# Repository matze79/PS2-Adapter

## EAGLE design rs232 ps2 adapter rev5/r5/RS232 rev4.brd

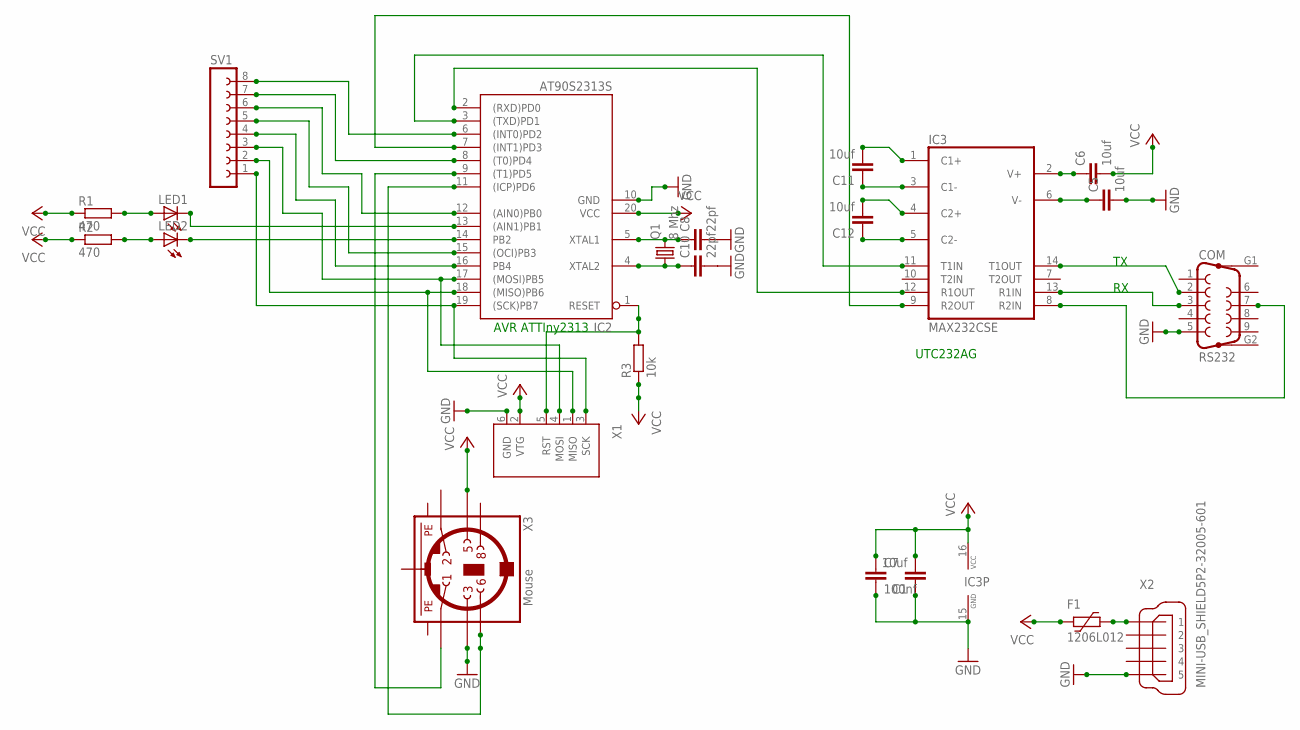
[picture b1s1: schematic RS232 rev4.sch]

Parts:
C1, C5, C6, C11, C12: 10uf; C1206K
C7: 100nf; C1206
C8, C10: 22pf; C1206
COM: RS232; F09HP
F1: 1206L012; 1206L
IC2: AT90S2313S; SO20L
IC3: MAX232CSE; SO16
LED1, LED2: LEDCHIPLED_0805; CHIPLED_0805
Q1: 8 Mhz; HC49/S
R1, R2: 470; R1206
R3: 10k; R1206
SV1: FE08-1; FE08
X1: AVRISP6PINHEADER; 6PINHEADER
X2: MINI-USB_SHIELD5P2-32005-601; 32005-601
X3: Mouse; M_DIN6

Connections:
GND: C1.1, C5.2, C7.2, C8.2, C10.2, COM.5, IC2.10 (GND), IC3.15 (GND), X1.6 (GND), X2.5, X3.3
unnamed: IC2.3 ((TXD)PD1), IC3.11 (T1IN)
unnamed: IC2.2 ((RXD)PD0), IC3.12 (R1OUT)
unnamed: C11.1, IC3.3 (C1-)
unnamed: C11.2, IC3.1 (C1+)
unnamed: C12.2, IC3.4 (C2+)
unnamed: C12.1, IC3.5 (C2-)
unnamed: IC2.1 (RESET), R3.2, X1.5 (RST)
unnamed: IC2.11 ((ICP)PD6), X3.6
unnamed: COM.2, IC3.14 (T1OUT)
unnamed: IC2.7 ((INT1)PD3), IC3.9 (R2OUT)
unnamed: C8.1, IC2.5 (XTAL1), Q1.2
unnamed: IC2.14 (PB2), LED2.C
unnamed: C5.1, IC3.6 (V-)
unnamed: C6.1, IC3.2 (V+)
unnamed: IC2.13 ((AIN1)PB1), LED1.C
unnamed: COM.3, IC3.13 (R1IN)
unnamed: C10.1, IC2.4 (XTAL2), Q1.1
unnamed: LED2.A, R2.2
unnamed: LED1.A, R1.2
unnamed: IC2.9 ((T1)PD5), X3.1
unnamed: F1.1, X2.1
PB2: IC2.12 ((AIN0)PB0), SV1.6
PB3: IC2.15 ((OCI)PB3), SV1.5
PB4: IC2.16 (PB4), SV1.4
PB5: IC2.17 ((MOSI)PB5), SV1.3, X1.4 (MOSI)
PB6: IC2.18 ((MISO)PB6), SV1.2, X1.1 (MISO)
PB7: IC2.19 ((SCK)PB7), SV1.1, X1.3 (SCK)
PD2: IC2.6 ((INT0)PD2), SV1.8
PD4: IC2.8 ((T0)PD4), SV1.7
PE1: X3.SH1 (PE1)
PE2: X3.SH2 (PE2)
PE3: X3.SH3 (PE3)
SERIAL#: COM.7, IC3.8 (R2IN)
VCC: C1.2, C6.2, C7.1, F1.2, IC2.20 (VCC), IC3.16 (VCC), R1.1, R2.1, R3.1, X1.2 (VTG), X3.5

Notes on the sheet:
AVR ATTIny2313
UTC232AG

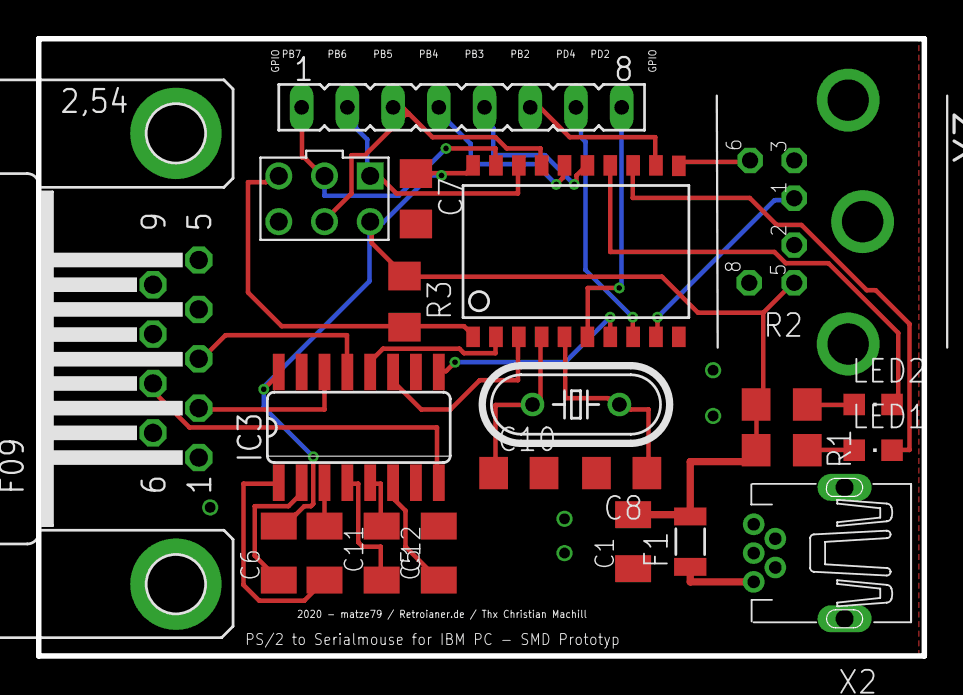
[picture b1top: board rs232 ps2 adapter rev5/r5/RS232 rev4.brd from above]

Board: 2 copper layers, 49.2 x 34.3 mm, 22 parts (0 on the bottom side), 32 nets.

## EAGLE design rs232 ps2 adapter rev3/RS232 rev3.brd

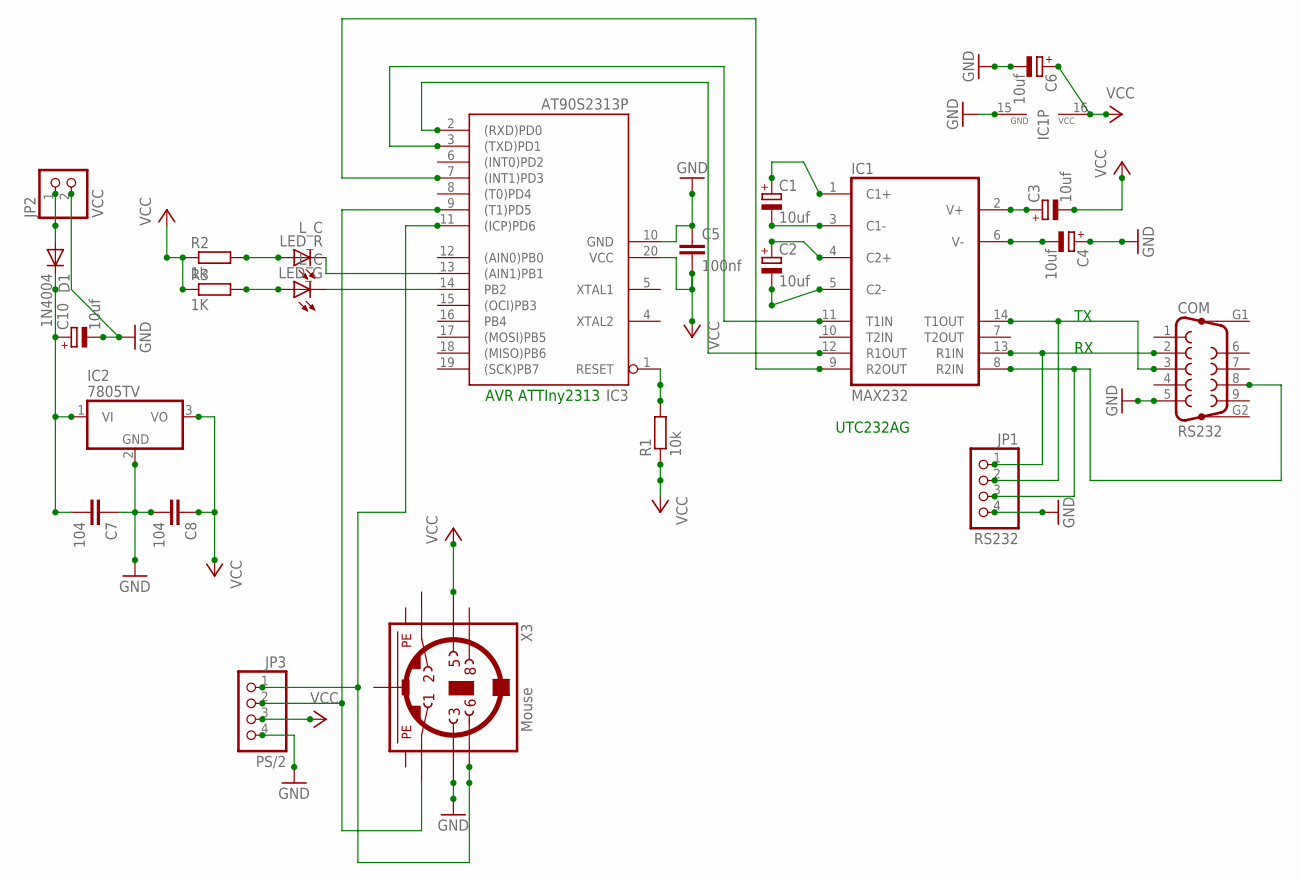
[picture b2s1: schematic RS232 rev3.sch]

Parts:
C1, C2, C3, C4, C6, C10: 10uf; E2,5-6E
C5: 100nf; C2.5-3
C7, C8: 104; C025-025X050
COM: RS232; F09HP
D1: 1N4004; DO41-10
IC1: MAX232; DIL16
IC2: 7805TV; TO220V
IC3: AT90S2313P; DIL20
JP1: RS232; 1X04
JP2: VCC; 1X02
JP3: PS/2; 1X04
LED_G: L_C; LED3MM
LED_R: L_C; LED3MM
R1: 10k; 0207/7
R2: 1k; 0309V
R3: 1K; 0309V
X3: Mouse; M_DIN6

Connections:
GND: C4.+, C5.1, C6.-, C7.1, C8.2, C10.-, COM.5, IC1.15 (GND), IC2.2 (GND), IC3.10 (GND), JP1.4, JP2.2, JP3.4, X3.3
unnamed: IC1.11 (T1IN), IC3.3 ((TXD)PD1)
unnamed: IC1.12 (R1OUT), IC3.2 ((RXD)PD0)
unnamed: C1.-, IC1.3 (C1-)
unnamed: C1.+, IC1.1 (C1+)
unnamed: C2.+, IC1.4 (C2+)
unnamed: C2.-, IC1.5 (C2-)
unnamed: IC3.1 (RESET), R1.2
unnamed: IC3.11 ((ICP)PD6), JP3.1, X3.6
unnamed: C7.2, C10.+, D1.C, IC2.1 (VI)
unnamed: IC1.9 (R2OUT), IC3.7 ((INT1)PD3)
unnamed: IC3.14 (PB2), LED_G.K (C)
unnamed: C4.-, IC1.6 (V-)
unnamed: C3.+, IC1.2 (V+)
unnamed: IC3.13 ((AIN1)PB1), LED_R.K (C)
unnamed: COM.2, IC1.13 (R1IN), JP1.1
unnamed: COM.3, IC1.14 (T1OUT), JP1.2
unnamed: LED_G.A, R3.2
unnamed: LED_R.A, R2.2
unnamed: IC3.9 ((T1)PD5), JP3.2, X3.1
PE1: X3.SH1 (PE1)
PE2: X3.SH2 (PE2)
PE3: X3.SH3 (PE3)
POWER: D1.A, JP2.1
SERIAL#: COM.8, IC1.8 (R2IN), JP1.3
VCC: C3.-, C5.2, C6.+, C8.1, IC1.16 (VCC), IC2.3 (VO), IC3.20 (VCC), JP3.3, R1.1, R2.1, R3.1, X3.5

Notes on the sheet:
AVR ATTIny2313
UTC232AG

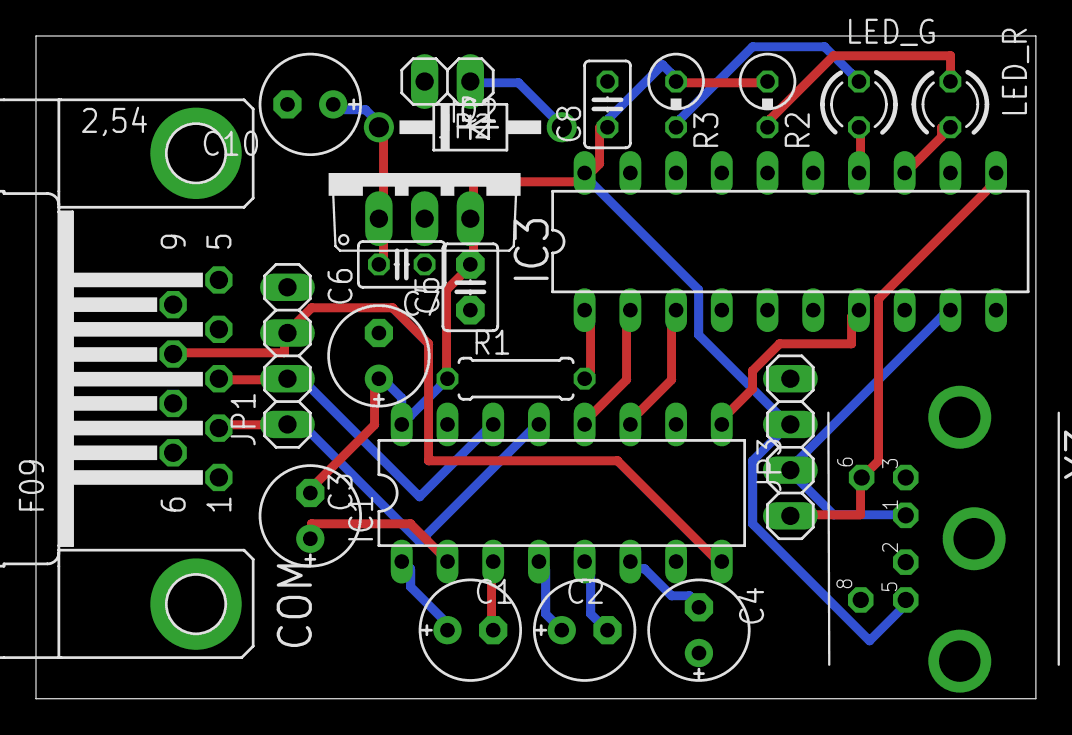
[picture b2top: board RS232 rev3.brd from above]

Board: 2 copper layers, 55.6 x 36.8 mm, 23 parts (0 on the bottom side), 23 nets.

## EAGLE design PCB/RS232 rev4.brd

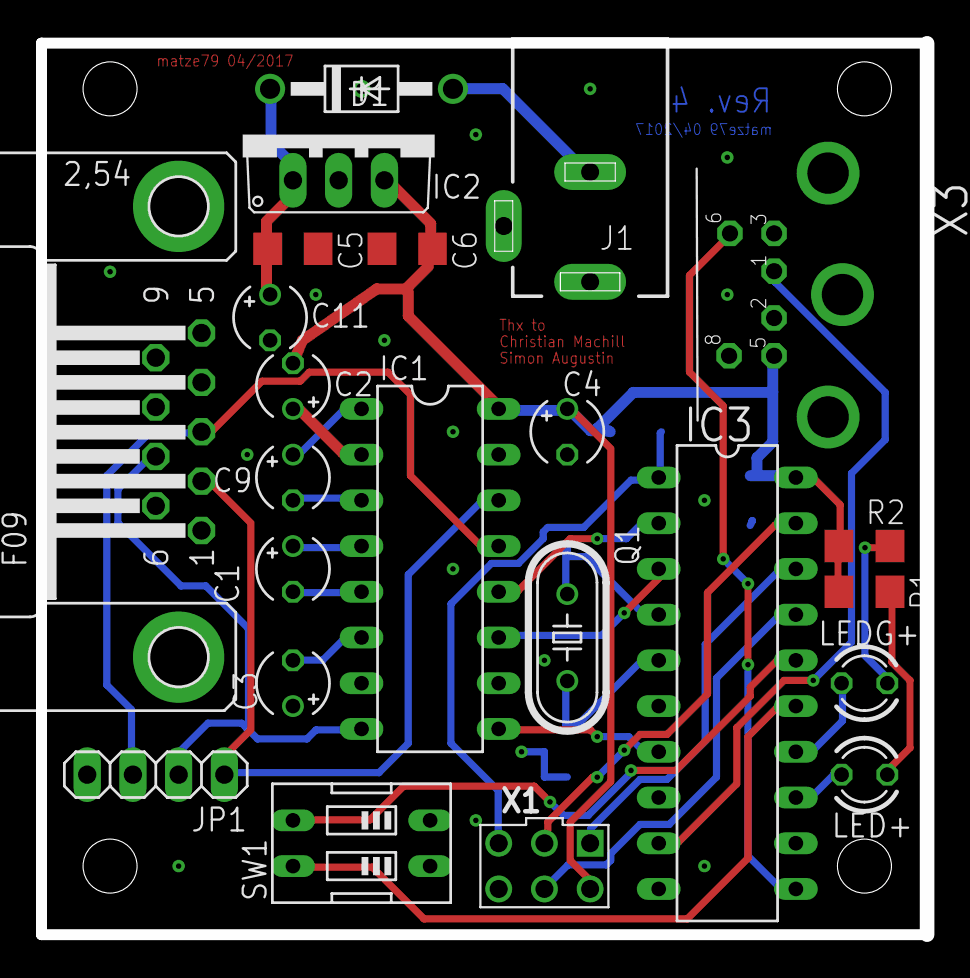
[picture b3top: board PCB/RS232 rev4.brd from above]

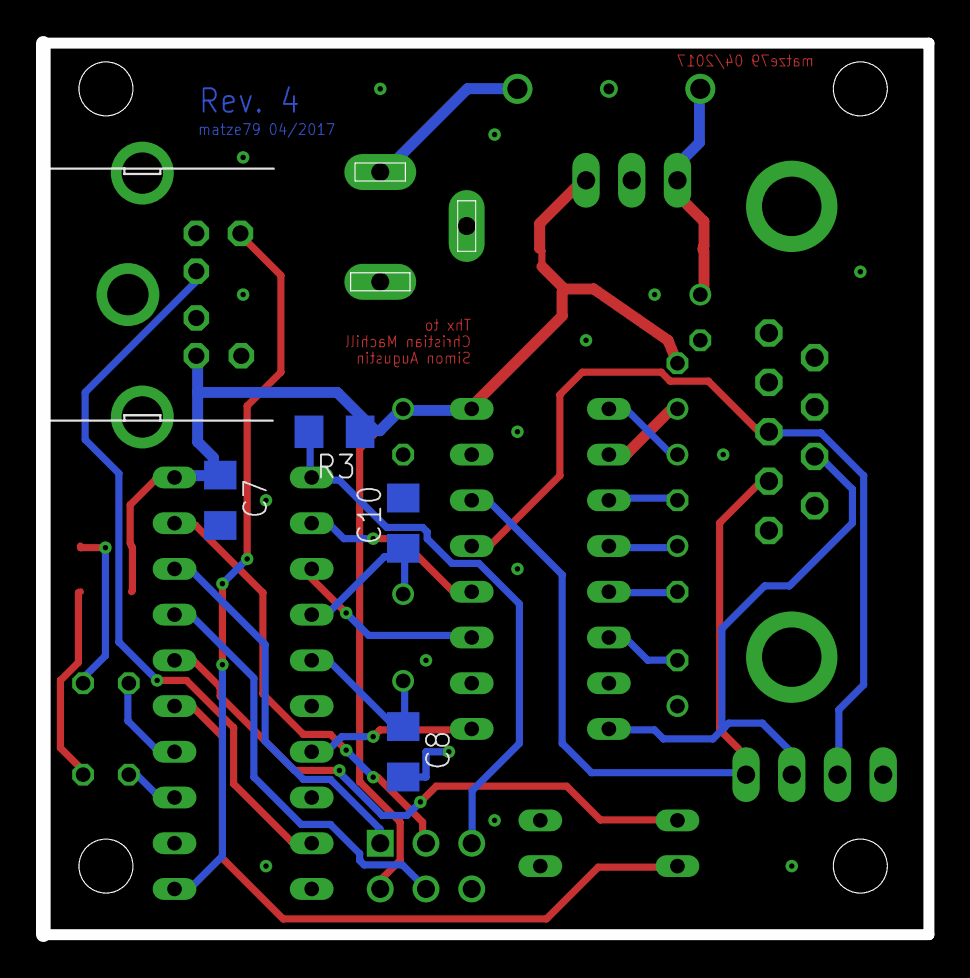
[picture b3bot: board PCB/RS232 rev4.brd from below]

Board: 2 copper layers, 49.1 x 49.5 mm, 27 parts (4 on the bottom side), 30 nets.

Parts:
C1, C2, C3, C4, C9: 10uf; TT2D4
C5, C6, C7: 100nf; C1206
C8, C10: 22pf; C1206
C11: 100uf; TT2D4
COM: RS232; F09HP
D1: 1N4004; DO41-10
IC1: MAX232; DIL16
IC2: 7805TV; TO220V
IC3: AT90S2313P; DIL20
J1: DCJ0202
JP1: RS232; 1X04
LED+: L_C; LED3MM
LEDG+: L_C; LED3MM
Q1: 8 Mhz; HC49/S
R1, R2: 470; R1206
R3: 10k; R1206
SW1: DIP; EDG-02
X1: AVRISP6PINHEADER; 6PINHEADER
X3: Mouse; M_DIN6

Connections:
GND: C3.+, C4.-, C5.2, C6.1, C7.2, C8.2, C10.2, C11.-, COM.5, IC1.15, IC2.2, IC3.10, J1.1, JP1.4, SW1.1, SW1.2, X1.6, X3.3
unnamed: IC1.11, IC3.3
unnamed: IC1.12, IC3.2
unnamed: C9.-, IC1.3
unnamed: C9.+, IC1.1
unnamed: C1.+, IC1.4
unnamed: C1.-, IC1.5
unnamed: IC3.1, R3.2, X1.5
unnamed: IC3.11, X3.6
unnamed: COM.2, IC1.14, JP1.1
unnamed: C5.1, C11.+, D1.C, IC2.1
unnamed: IC1.9, IC3.7
unnamed: C8.1, IC3.5, Q1.2
unnamed: IC3.14, LEDG+.K
unnamed: C3.-, IC1.6
unnamed: C2.+, IC1.2
unnamed: IC3.13, LED+.K
unnamed: COM.3, IC1.13, JP1.3
unnamed: C10.1, IC3.4, Q1.1
unnamed: IC3.16, SW1.3
unnamed: LEDG+.A, R2.2
unnamed: LED+.A, R1.2
unnamed: IC3.9, X3.1
unnamed: IC3.15, SW1.4
unnamed: IC3.19, X1.3
unnamed: IC3.17, X1.4
unnamed: IC3.18, X1.1
POWER: D1.A, J1.3
SERIAL#: COM.7, IC1.8, JP1.2
VCC: C2.-, C4.+, C6.2, C7.1, IC1.16, IC2.3, IC3.20, R1.1, R2.1, R3.1, X1.2, X3.5

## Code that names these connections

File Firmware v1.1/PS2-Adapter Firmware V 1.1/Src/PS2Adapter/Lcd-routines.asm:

;;;;;;;;;;;;;;;;;;;;;;;;;;;;;;;;;;;;;;;;;;;;;;;;;
;;                 LCD-Routinen                ;;
;;                 ============                ;;
;;              (c)andreas-s@web.de            ;;
;;                                             ;;
;; 4bit-Interface                              ;;
;; DB4-DB7:       PD0-PD3                      ;;
;; RS:            PD4                          ;;
;; E:             PD5                          ;;
;;;;;;;;;;;;;;;;;;;;;;;;;;;;;;;;;;;;;;;;;;;;;;;;;
.def temp1 = r24
.def temp2 = r22
.def temp3 = r23
 
.equ LCD_PORT = PORTB
.equ LCD_DDR  = DDRB
.equ PIN_RS   = 4
.equ PIN_E    = 5

.ifndef XTAL
.equ XTAL = 1000000
.endif

 ;sendet ein Datenbyte an das LCD
lcd_data:
           push  temp2
           push  temp3
           mov   temp2, temp1            ; "Sicherungskopie" für
                                         ; die Übertragung des 2.Nibbles
           swap  temp1                   ; Vertauschen
           andi  temp1, 0b00001111       ; oberes Nibble auf Null setzen
           sbr   temp1, 1<<PIN_RS        ; entspricht 0b00010000
           in    temp3, LCD_PORT
           andi  temp3, 0xC0
           or    temp1, temp3
           out   LCD_PORT, temp1         ; ausgeben
           rcall lcd_enable              ; Enable-Routine aufrufen
                                         ; 2. Nibble, kein swap da es schon
                                         ; an der richtigen stelle ist
           andi  temp2, 0b00001111       ; obere Hälfte auf Null setzen 
           sbr   temp2, 1<<PIN_RS        ; entspricht 0b00010000
           or    temp2, temp3
           out   LCD_PORT, temp2         ; ausgeben
           rcall lcd_enable              ; Enable-Routine aufrufen
           rcall delay50us               ; Delay-Routine aufrufen

           pop   temp3
           pop   temp2
           ret                           ; zurück zum Hauptprogramm
 
 ; sendet einen Befehl an das LCD
lcd_command:                            ; wie lcd_data, nur ohne RS zu setzen
           push  temp2
           push  temp3

           mov   temp2, temp1
           swap  temp1
           andi  temp1, 0b00001111
           in    temp3, LCD_PORT
           andi  temp3, 0x80
           or    temp1, temp3
           out   LCD_PORT, temp1
           rcall lcd_enable
           andi  temp2, 0b00001111
           or    temp2, temp3
           out   LCD_PORT, temp2
           rcall lcd_enable
           rcall delay50us
 
           pop   temp3
           pop   temp2
           ret
 
 ; erzeugt den Enable-Puls
lcd_enable:
           sbi LCD_PORT, PIN_E          ; Enable high
           nop                          ; 3 Taktzyklen warten
           nop
           nop
           cbi LCD_PORT, PIN_E          ; Enable wieder low
           ret                          ; Und wieder zurück                     
 
 ; Pause nach jeder Übertragung
delay50us:                              ; 50us Pause
           ldi  temp1, ( XTAL * 50 / 3 ) / 1000000
delay50us_:
           dec  temp1
           brne delay50us_
           ret                          ; wieder zurück
 
 ; Längere Pause für manche Befehle
delay5ms:                               ; 5ms Pause
           ldi  temp1, ( XTAL * 5 / 607 ) / 1000
WGLOOP0:   ldi  temp2, $C9
WGLOOP1:   dec  temp2
           brne WGLOOP1
           dec  temp1
           brne WGLOOP0
           ret                          ; wieder zurück
 
 ; Initialisierung: muss ganz am Anfang des Programms aufgerufen werden
lcd_init:
           push  temp1
           in    temp1, LCD_DDR
           ori   temp1, (1<<PIN_E) | (1<<PIN_RS) | 0x0F
           out   LCD_DDR, temp1

           ldi   temp3,6
powerupwait:
           rcall delay5ms
           dec   temp3
           brne  powerupwait

           ldi   temp1,    0b00000011   ; muss 3mal hintereinander gesendet
           out   LCD_PORT, temp1        ; werden zur Initialisierung

           rcall lcd_enable             ; 1
           rcall delay5ms

           rcall lcd_enable             ; 2
           rcall delay5ms

           rcall lcd_enable             ; und 3!
           rcall delay5ms

           ldi   temp1,    0b00000010   ; 4bit-Modus einstellen
           out   LCD_PORT, temp1
           rcall lcd_enable
           rcall delay5ms
		   
           ldi   temp1,    0b00101000   ; 4 Bot, 2 Zeilen
           rcall lcd_command
           ldi   temp1,    0b00001100   ; Display on, Cursor off
           rcall lcd_command
           ldi   temp1,    0b00000100   ; endlich fertig
           rcall lcd_command

           pop   temp1
           ret
 
 ; Sendet den Befehl zur Löschung des Displays
lcd_clear:
           push  temp1
           ldi   temp1,    0b00000001   ; Display löschen
           rcall lcd_command
           rcall delay5ms
           pop   temp1
           ret

 ; Cursor Home
lcd_home:
           push  temp1
           ldi   temp1,    0b00000010   ; Cursor Home
           rcall lcd_command
           rcall delay5ms
           pop   temp1
           ret

 ; Einen konstanten Text aus dem Flash Speicher
 ; ausgeben. Der Text wird mit einer 0 beendet
lcd_flash_string:
           push  temp1

lcd_flash_string_1:
           lpm   temp1, Z+
           cpi   temp1, 0
           breq  lcd_flash_string_2
           rcall  lcd_data
           rjmp  lcd_flash_string_1

lcd_flash_string_2:
           pop   temp1
           ret

 ; Eine Zahl aus dem Register temp1 dezimal ausgeben
lcd_number:
           push  temp1
           push  temp2
           push  temp3

           mov   temp2, temp1
                                  ; abzählen wieviele Hunderter
                                          ; in der Zahl enthalten sind
           ldi   temp1, '0'
lcd_number_1:
           subi  temp2, 100
           brcs  lcd_number_2
           inc   temp1
           rjmp  lcd_number_1
                                          ;
                                          ; die Hunderterstelle ausgeben
lcd_number_2:
           rcall lcd_data
           subi  temp2, -100              ; 100 wieder dazuzählen, da die
                                          ; vorherhgehende Schleife 100 zuviel
                                          ; abgezogen hat

                                          ; abzählen wieviele Zehner in
                                          ; der Zahl enthalten sind
           ldi   temp1, '0'
lcd_number_3:
           subi  temp2, 10
           brcs  lcd_number_4
           inc   temp1
           rjmp  lcd_number_3

                                          ; die Zehnerstelle ausgeben
lcd_number_4:
           rcall lcd_data
           subi  temp2, -10               ; 10 wieder dazuzählen, da die
                                          ; vorhergehende Schleife 10 zuviel
                                          ; abgezogen hat

                                          ; die übrig gebliebenen Einer
                                          ; noch ausgeben
           ldi   temp1, '0'
           add   temp1, temp2
           rcall lcd_data

           pop   temp3
           pop   temp2
           pop   temp1
           ret

; eine Zahl aus dem Register temp1 hexadezimal ausgeben
lcd_number_hex:
           push  temp1

           swap  temp1
           andi  temp1, $0F
           rcall lcd_number_hex_digit

           pop   temp1
           push  temp1

           andi  temp1, $0F
           rcall lcd_number_hex_digit

           pop   temp1
           ret

lcd_number_hex_digit:
           cpi   temp1, 10
           brlt  lcd_number_hex_digit_1
           subi  temp1, -( 'A' - '9' - 1 )
lcd_number_hex_digit_1:
           subi  temp1, -'0'
           rcall  lcd_data
           ret

  

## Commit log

2018-05-23 PCB Files and 3d printed Case
    Added PCB and Schematic.
    DIP Switch is useless, no support in Firmware.
2018-09-18 Add files via upload
    Precompiled Firmware for tiny2313
    flash with:
    avrdude -c usbasp -p t2313 -U lfuse:w:0xfd:m -U hfuse:w:0xdf:m -U efuse:w:0xfe:m
    avrdude -c usbasp -p t2313 -U flash:w:ps2adapter-noboot-tiny2313.hex
2019-02-23 Firmware Version Bump
2019-02-23 Wrong Version
2020-10-04 Add files via upload
    Script for flashing with AVRDUDE, Board Revision 4
2020-10-04 Add files via upload
    Script for flashing Revision 6, SMD
2021-01-03 Add files via upload
    translated to english
2025-11-23 PS2 Adapter

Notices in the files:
parts and their libraries:
SparkFun-Clocks: Licensing: Creative Commons ShareAlike 4.0 International - https://creativecommons.org/licenses/by-sa/4.0
